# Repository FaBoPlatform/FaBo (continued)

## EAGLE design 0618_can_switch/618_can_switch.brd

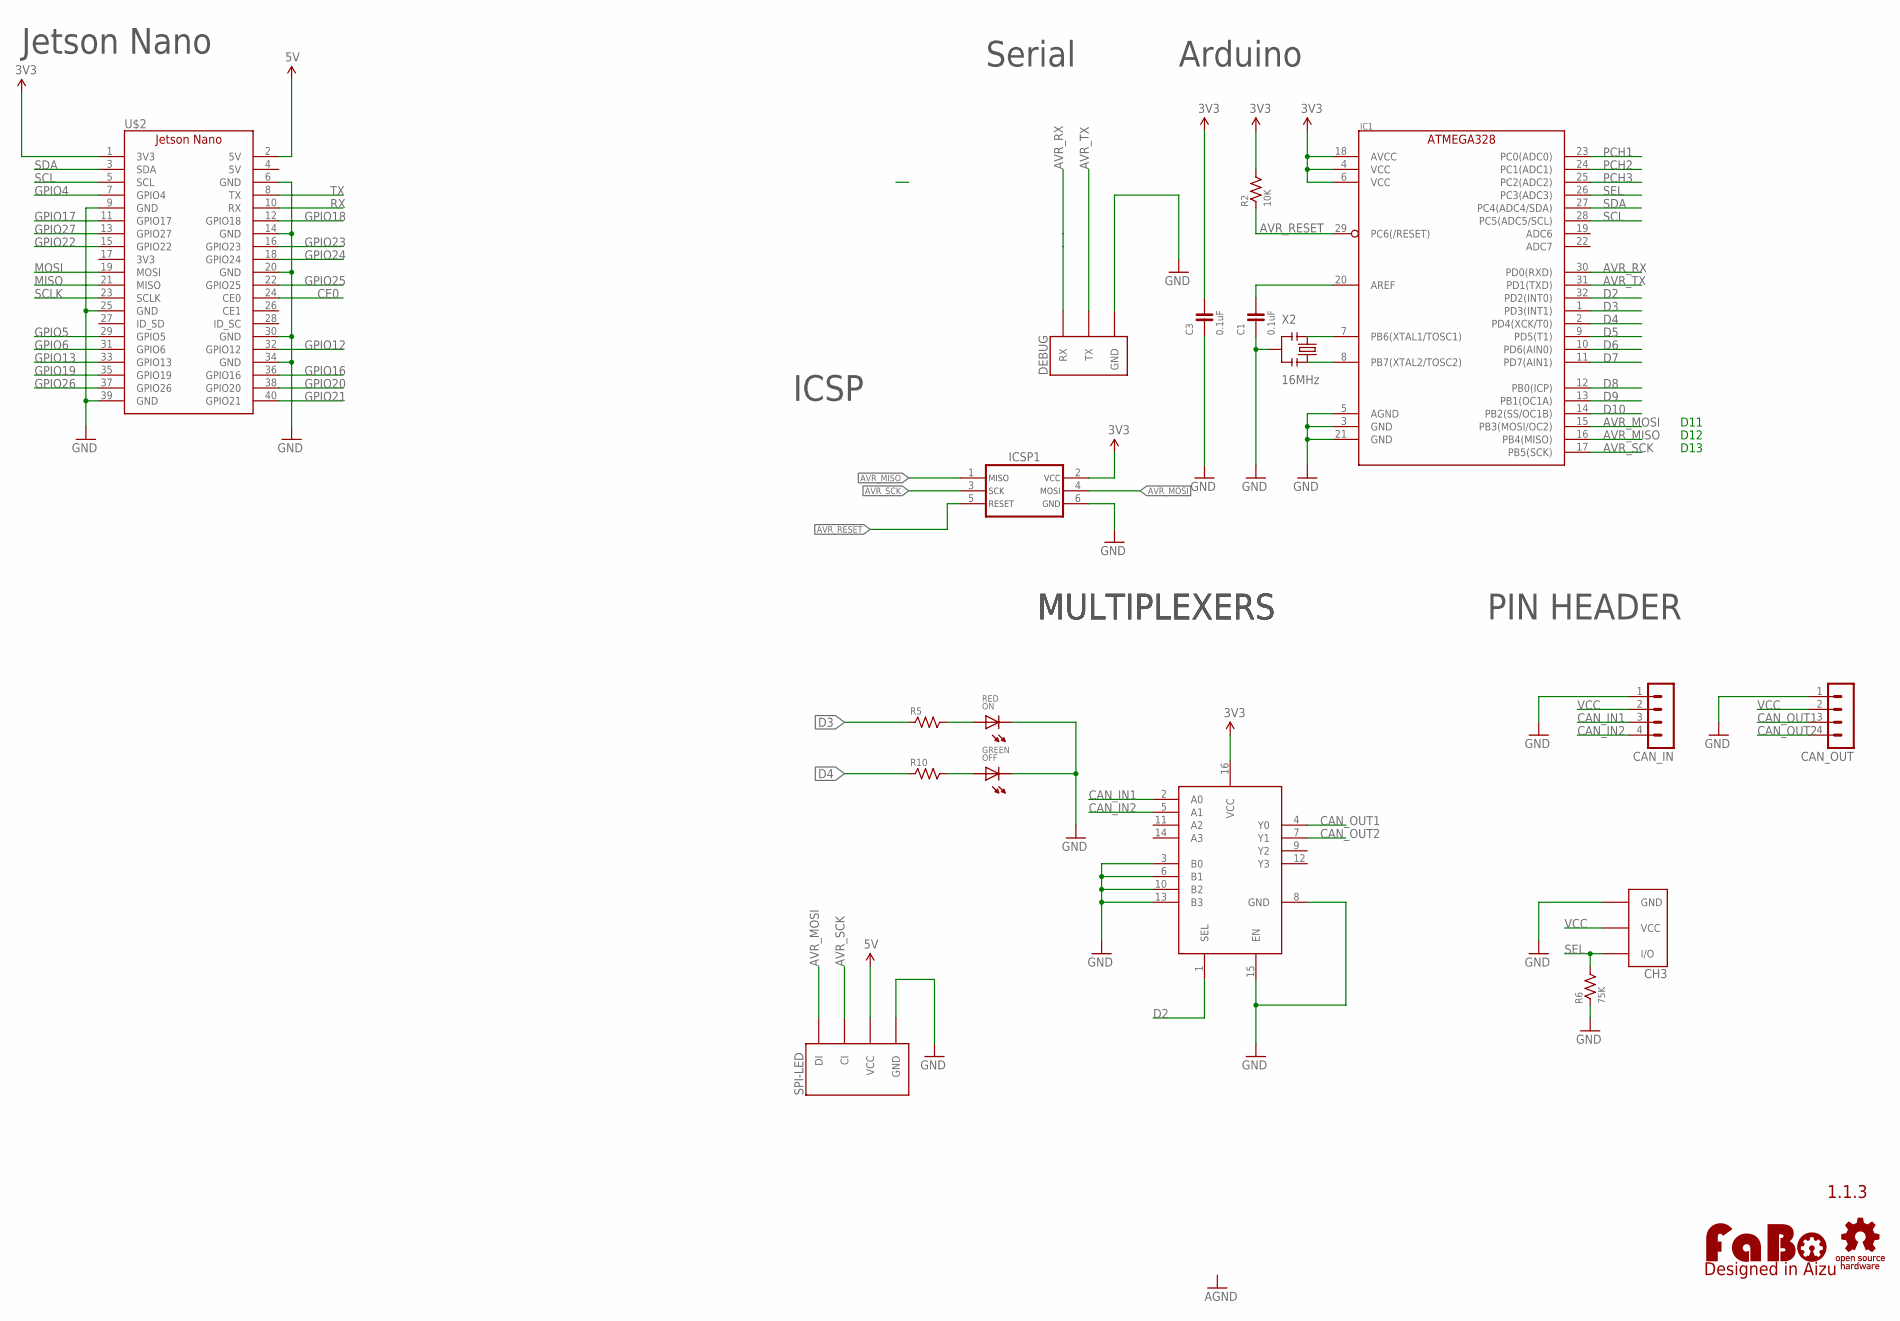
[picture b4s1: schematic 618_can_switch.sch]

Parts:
C1, C3: 0.1uF; 0603
CAN_IN: MA04-1
CAN_OUT: MA04-1
CH3: FABO_BRICK_3PIN-HEADER; FABO_BRICK_3PIN_HEADER
DEBUG: FABO_BRICK_3PIN_DEBUG
IC1: ATMEGA328P-AU; TQFP-32
IC3: MULTIPLEXERSMC74HC157A; TSSOP-16
ICSP1: ICSP_AVR-TC_NOHOLE; TC2030
LOGO1: LOGO_FABO-S; LOGO_FABO_S
OFF: GREEN; 0603
ON: RED; 0603
R2: 10K; 0603
R5, R10: 220; 0603
R6: 75K; 0603
SPI-LED: FABO-SPI-LED-B04B; SPI-B04B-PASK-1
U$2: JETSON_NANO_NOBORDER; JETSON_NANO_NOBOARDER
U$7: LOGO_OSHW-M_BOTTOM; LOGO_OSHW_M_BOTTOM
X2: 16MHz; CSTNE_V_C

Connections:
3V3: C3.2, IC1.4 (VCC), IC1.6 (VCC), IC1.18 (AVCC), IC3.16 (VCC), ICSP1.2, R2.2, U$2.1 (3V3)
5V: SPI-LED.VCC, U$2.2 (5V)
AVR_MISO: IC1.16 (PB4(MISO)), ICSP1.1
AVR_MOSI: IC1.15 (PB3(MOSI/OC2)), ICSP1.4, SPI-LED.DI
AVR_RESET: IC1.29 (PC6(/RESET)), ICSP1.5, R2.1
AVR_RX: DEBUG.RX, IC1.30 (PD0(RXD))
AVR_SCK: IC1.17 (PB5(SCK)), ICSP1.3, SPI-LED.CI
AVR_TX: DEBUG.TX, IC1.31 (PD1(TXD))
CAN_IN1: CAN_IN.3, IC3.2 (A0)
CAN_IN2: CAN_IN.4, IC3.5 (A1)
CAN_OUT1: CAN_OUT.3, IC3.4 (Y0)
CAN_OUT2: CAN_OUT.4, IC3.7 (Y1)
CE0: U$2.24 (CE0)
D2: IC1.32 (PD2(INT0)), IC3.1 (SEL)
D3: IC1.1 (PD3(INT1)), R5.1
D4: IC1.2 (PD4(XCK/T0)), R10.1
D5: IC1.9 (PD5(T1))
D6: IC1.10 (PD6(AIN0))
D7: IC1.11 (PD7(AIN1))
D8: IC1.12 (PB0(ICP))
D9: IC1.13 (PB1(OC1A))
D10: IC1.14 (PB2(SS/OC1B))
GND: C1.1, C3.1, CAN_IN.1, CAN_OUT.1, CH3.GND, DEBUG.GND, IC1.3 (GND), IC1.5 (AGND), IC1.21 (GND), IC3.3 (B0), IC3.6 (B1), IC3.8 (GND), IC3.10 (B2), IC3.13 (B3), IC3.15 (EN), ICSP1.6, OFF.CATHODE, ON.CATHODE, R6.1, SPI-LED.GND, U$2.6 (GND), U$2.9 (GND), U$2.14 (GND), U$2.20 (GND), U$2.25 (GND), U$2.30 (GND), U$2.34 (GND), U$2.39 (GND), X2.2
GPIO4: U$2.7 (GPIO4)
GPIO5: U$2.29 (GPIO5)
GPIO6: U$2.31 (GPIO6)
GPIO12: U$2.32 (GPIO12)
GPIO13: U$2.33 (GPIO13)
GPIO16: U$2.36 (GPIO16)
GPIO17: U$2.11 (GPIO17)
GPIO18: U$2.12 (GPIO18)
GPIO19: U$2.35 (GPIO19)
GPIO20: U$2.38 (GPIO20)
GPIO21: U$2.40 (GPIO21)
GPIO22: U$2.15 (GPIO22)
GPIO23: U$2.16 (GPIO23)
GPIO24: U$2.18 (GPIO24)
GPIO25: U$2.22 (GPIO25)
GPIO26: U$2.37 (GPIO26)
GPIO27: U$2.13 (GPIO27)
MISO: U$2.21 (MISO)
MOSI: U$2.19 (MOSI)
unnamed: C1.2, IC1.20 (AREF)
unnamed: IC1.8 (PB7(XTAL2/TOSC2)), X2.3
unnamed: IC1.7 (PB6(XTAL1/TOSC1)), X2.1
unnamed: ON.ANODE, R5.2
unnamed: OFF.ANODE, R10.2
PCH1: IC1.23 (PC0(ADC0))
PCH2: IC1.24 (PC1(ADC1))
PCH3: IC1.25 (PC2(ADC2))
RX: U$2.10 (RX)
SCL: IC1.28 (PC5(ADC5/SCL)), U$2.5 (SCL)
SCLK: U$2.23 (SCLK)
SDA: IC1.27 (PC4(ADC4/SDA)), U$2.3 (SDA)
SEL: CH3.I/O, IC1.26 (PC3(ADC3)), R6.2
TX: U$2.8 (TX)
VCC: CAN_IN.2, CAN_OUT.2, CH3.VCC

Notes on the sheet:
1.1.3
Jetson Nano
MULTIPLEXERS
PIN HEADER
D11
D12
D13
Arduino
Serial
ICSP

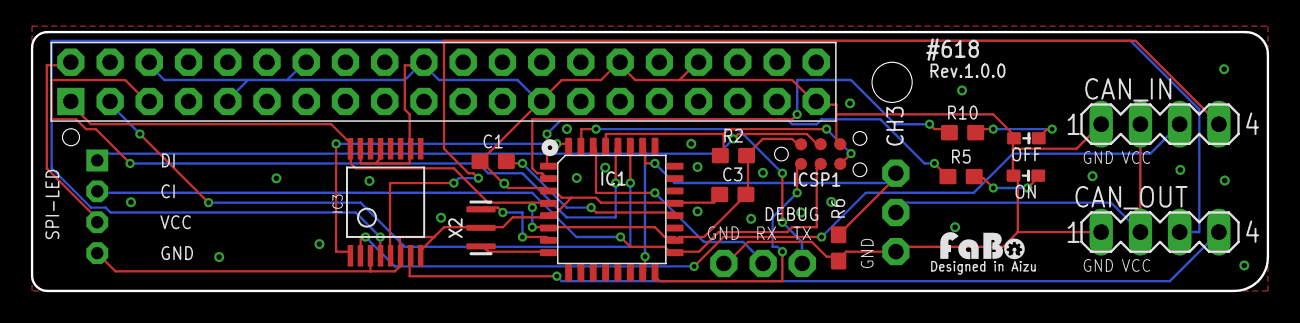
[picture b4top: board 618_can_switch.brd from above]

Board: 2 copper layers, 80.0 x 16.8 mm, 20 parts (0 on the bottom side), 25 nets.

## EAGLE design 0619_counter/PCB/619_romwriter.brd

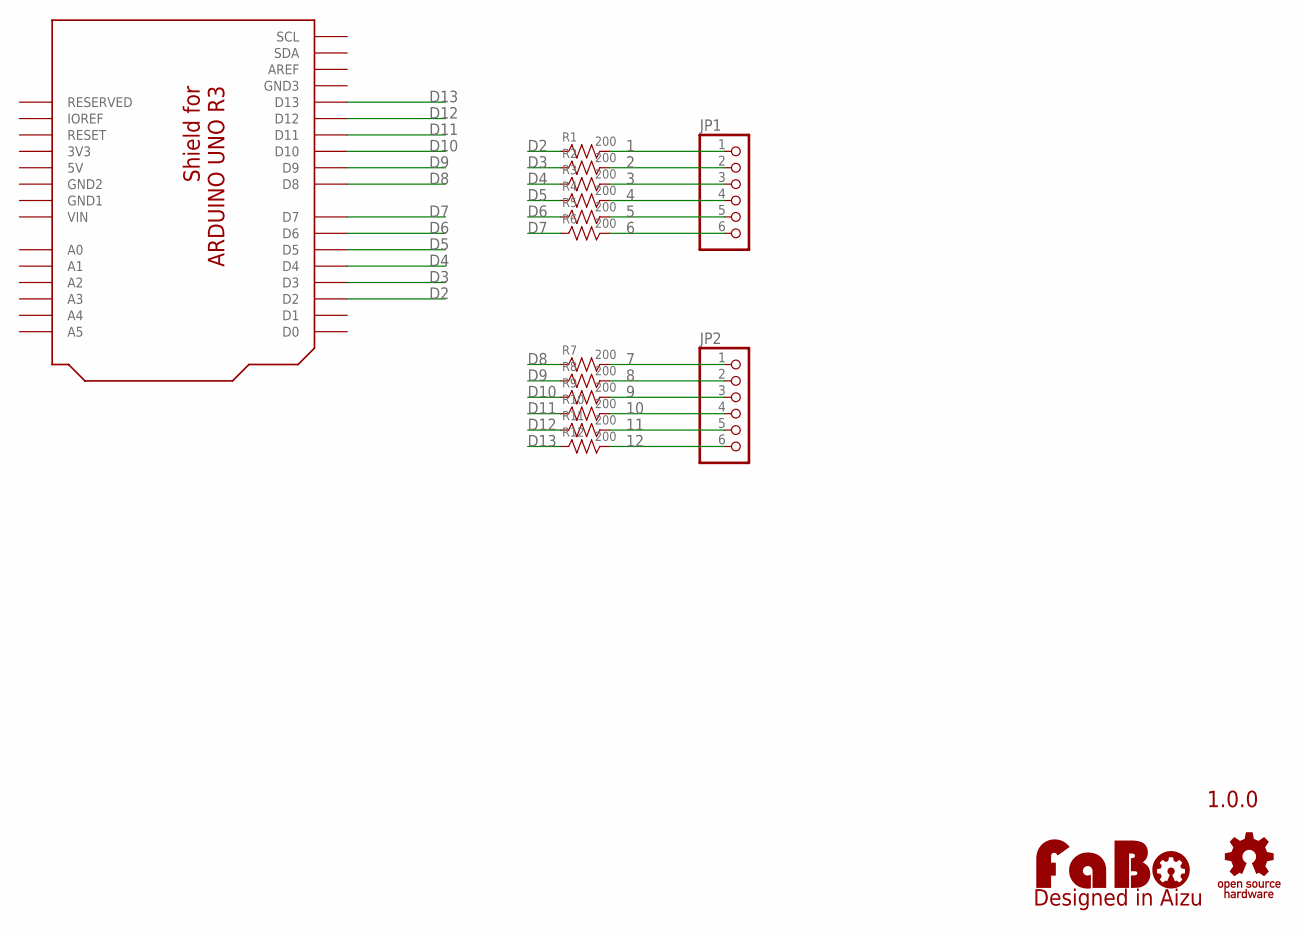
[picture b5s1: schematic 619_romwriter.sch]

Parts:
JP1, JP2: PINHD-1X6; 1X06
LOGO1: LOGO_FABO-M; LOGO_FABO_M
R1, R2, R3, R4, R5, R6, R7, R8, R9, R10, R11, R12: 200; 0603
U2: ARDUINO_UNO_R3_SHIELD-NOLABEL; ARDUINO_UNO_R3_NOLABEL
U$2: LOGO_OSHW-T_M; LOGO_OSHW_T_MS

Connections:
1: JP1.1, R1.2
2: JP1.2, R2.2
3: JP1.3, R3.2
3V3: U2.3V3
4: JP1.4, R4.2
5: JP1.5, R5.2
5V: U2.5V
6: JP1.6, R6.2
7: JP2.1, R7.2
8: JP2.2, R8.2
9: JP2.3, R9.2
10: JP2.4, R10.2
11: JP2.5, R11.2
12: JP2.6, R12.2
D2: R1.1, U2.D2
D3: R2.1, U2.D3
D4: R3.1, U2.D4
D5: R4.1, U2.D5
D6: R5.1, U2.D6
D7: R6.1, U2.D7
D8: R7.1, U2.D8
D9: R8.1, U2.D9
D10: R9.1, U2.D10
D11: R10.1, U2.D11
D12: R11.1, U2.D12
D13: R12.1, U2.D13
GND1: U2.GND1
GND2: U2.GND2
GND3: U2.GND3
VIN: U2.VIN

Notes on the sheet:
1.0.0

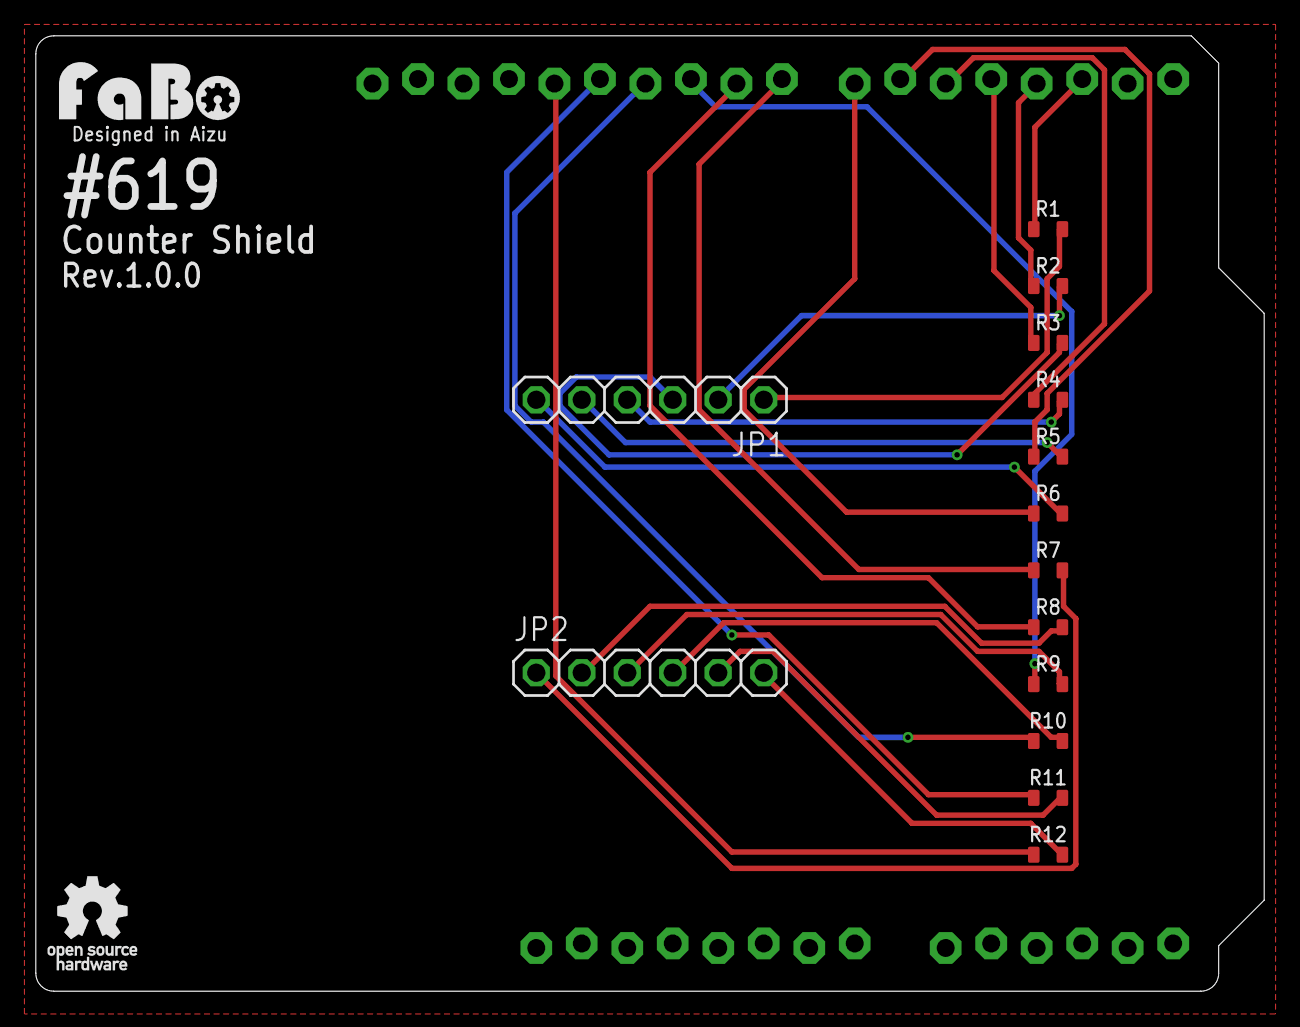
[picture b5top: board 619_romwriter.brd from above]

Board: 2 copper layers, 68.6 x 53.3 mm, 17 parts (0 on the bottom side), 24 nets.

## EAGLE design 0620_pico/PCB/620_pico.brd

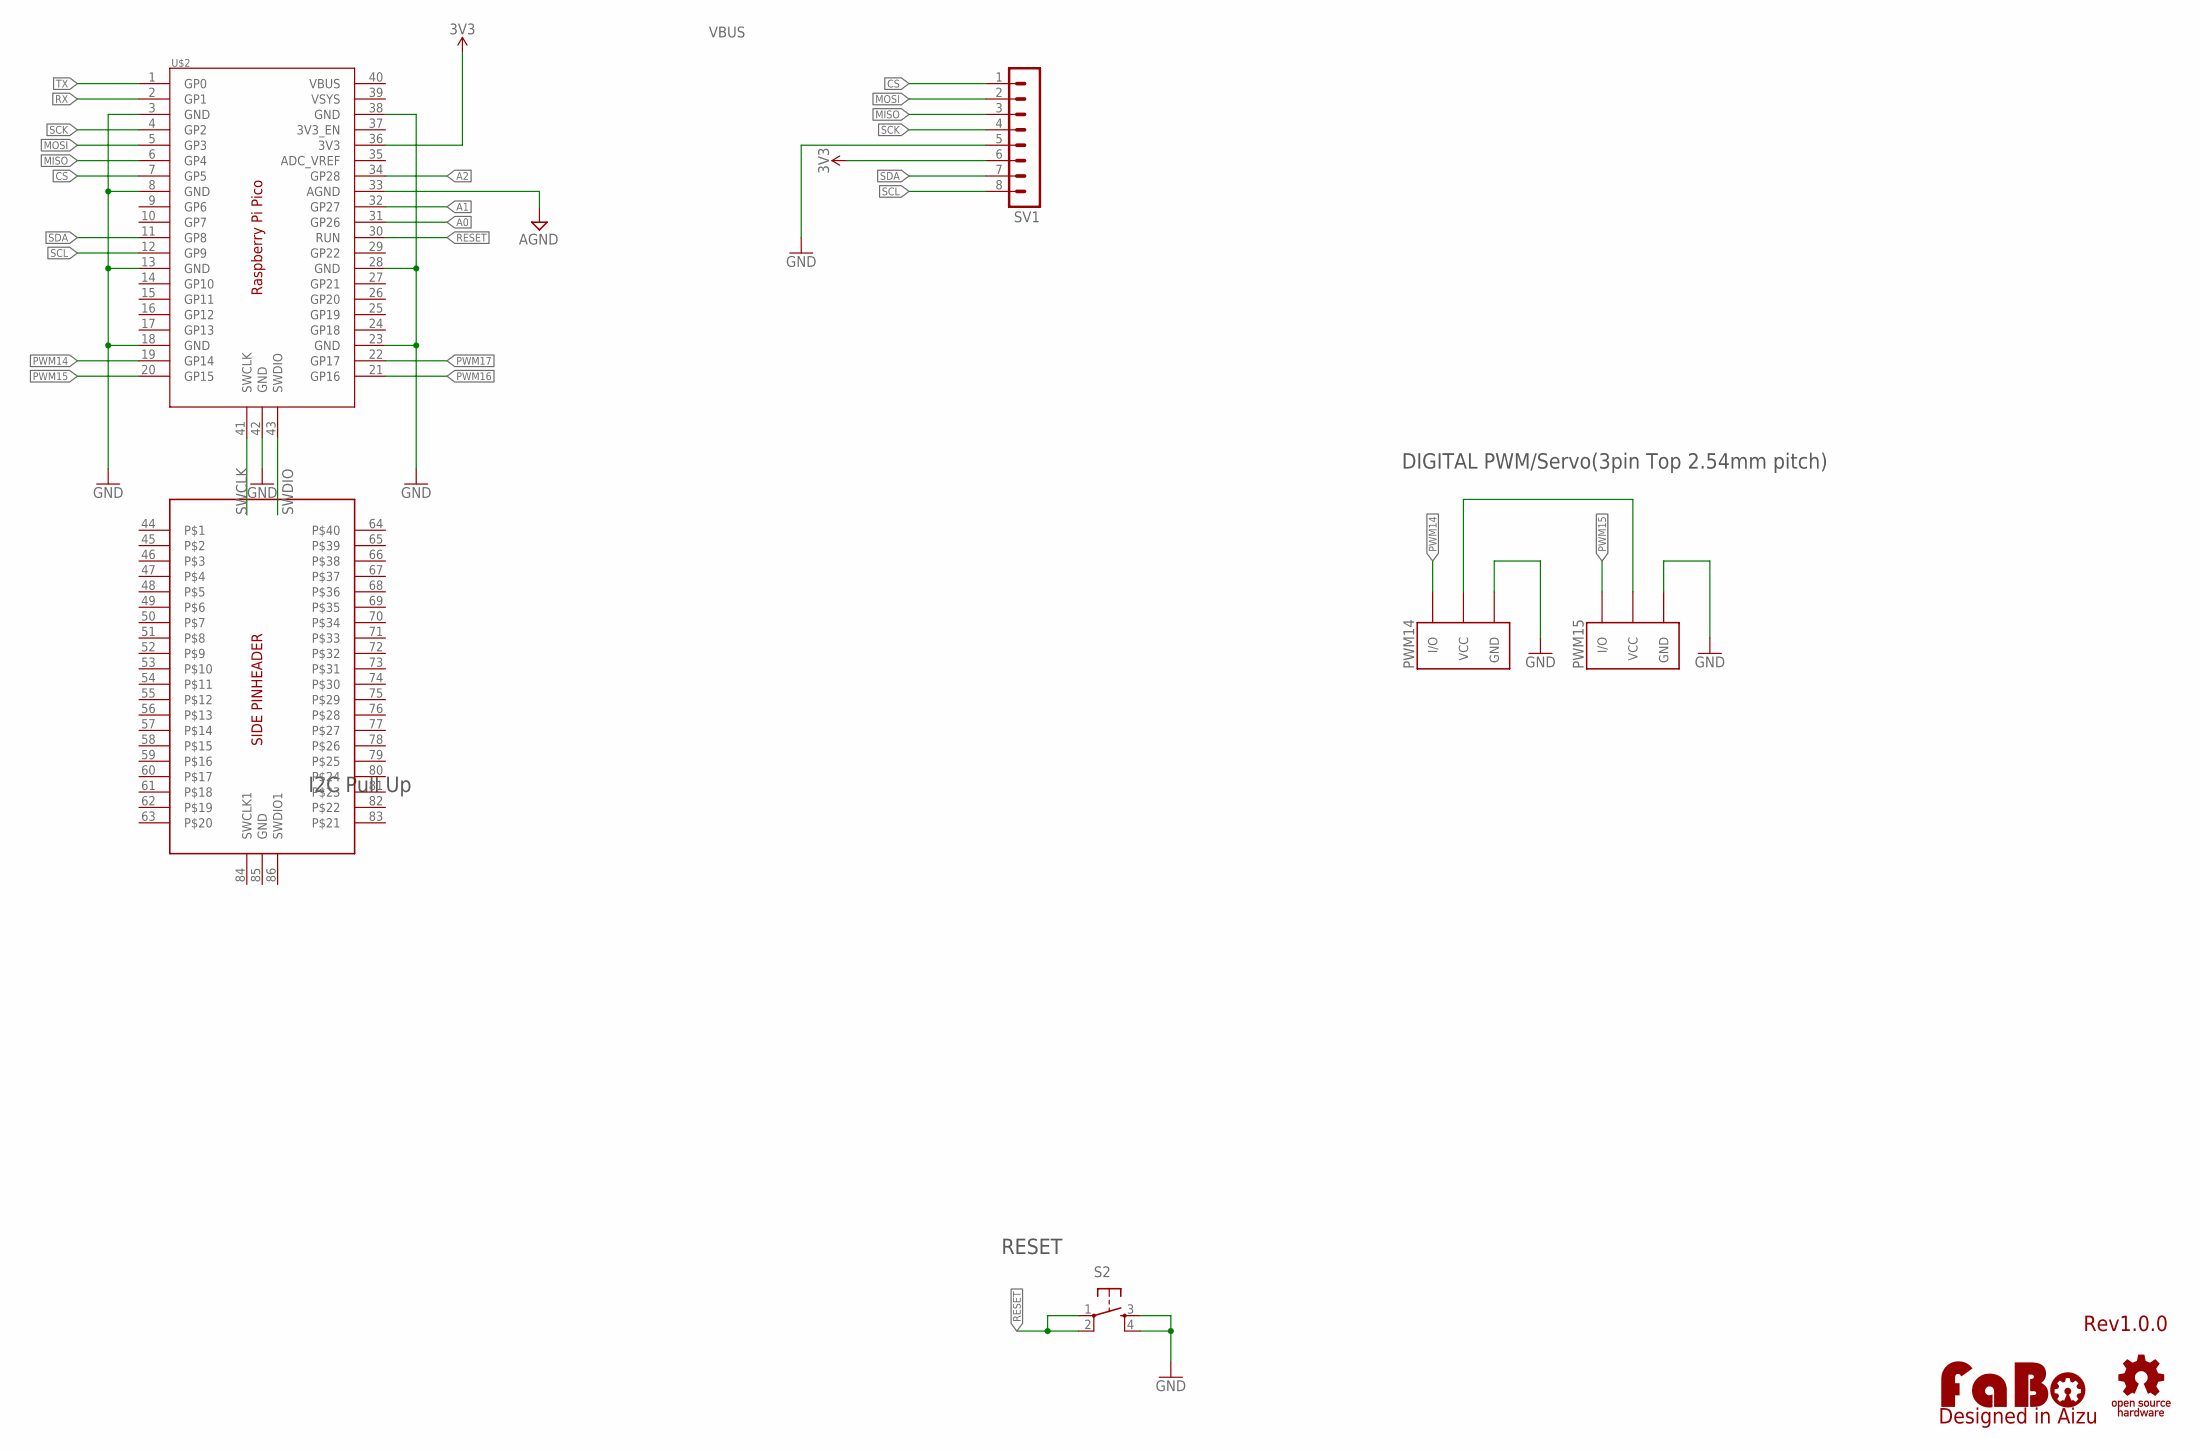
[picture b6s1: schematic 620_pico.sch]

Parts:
LOGO1: LOGO_OSHW-M_BOTTOM; LOGO_OSHW_M_BOTTOM
LOGO2: LOGO_FABO-M; LOGO_FABO_M
PWM14, PWM15: FABO_BRICK_3PIN-HEADER; FABO_BRICK_3PIN_HEADER
S2: TACT-SWITCH-SMD_KMR2; KMR2
SV1: MA08-1
U$2: RASPBERRY_PI_PICO_BOTH_TH_PINHEADER; RASPBERRY_PI_PICO_HEADER_BOTH

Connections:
3V3: SV1.6, U$2.36 (3V3)
A0: U$2.31 (GP26)
A1: U$2.32 (GP27)
A2: U$2.34 (GP28)
AGND: U$2.33 (AGND)
CS: SV1.1, U$2.7 (GP5)
GND: PWM14.GND, PWM15.GND, S2.3, S2.4, SV1.5, U$2.3 (GND), U$2.8 (GND), U$2.13 (GND), U$2.18 (GND), U$2.23 (GND), U$2.28 (GND), U$2.38 (GND), U$2.42 (GND)
MISO: SV1.3, U$2.6 (GP4)
MOSI: SV1.2, U$2.5 (GP3)
PWM14: PWM14.I/O, U$2.19 (GP14)
PWM15: PWM15.I/O, U$2.20 (GP15)
PWM16: U$2.21 (GP16)
PWM17: U$2.22 (GP17)
RESET: S2.1, S2.2, U$2.30 (RUN)
RX: U$2.2 (GP1)
SCK: SV1.4, U$2.4 (GP2)
SCL: SV1.8, U$2.12 (GP9)
SDA: SV1.7, U$2.11 (GP8)
SWCLK: U$2.41 (SWCLK)
SWDIO: U$2.43 (SWDIO)
TX: U$2.1 (GP0)
VBUS: PWM14.VCC, PWM15.VCC

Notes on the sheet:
Rev1.0.0
DIGITAL PWM/Servo(3pin Top 2.54mm pitch)
RESET
I2C Pull Up

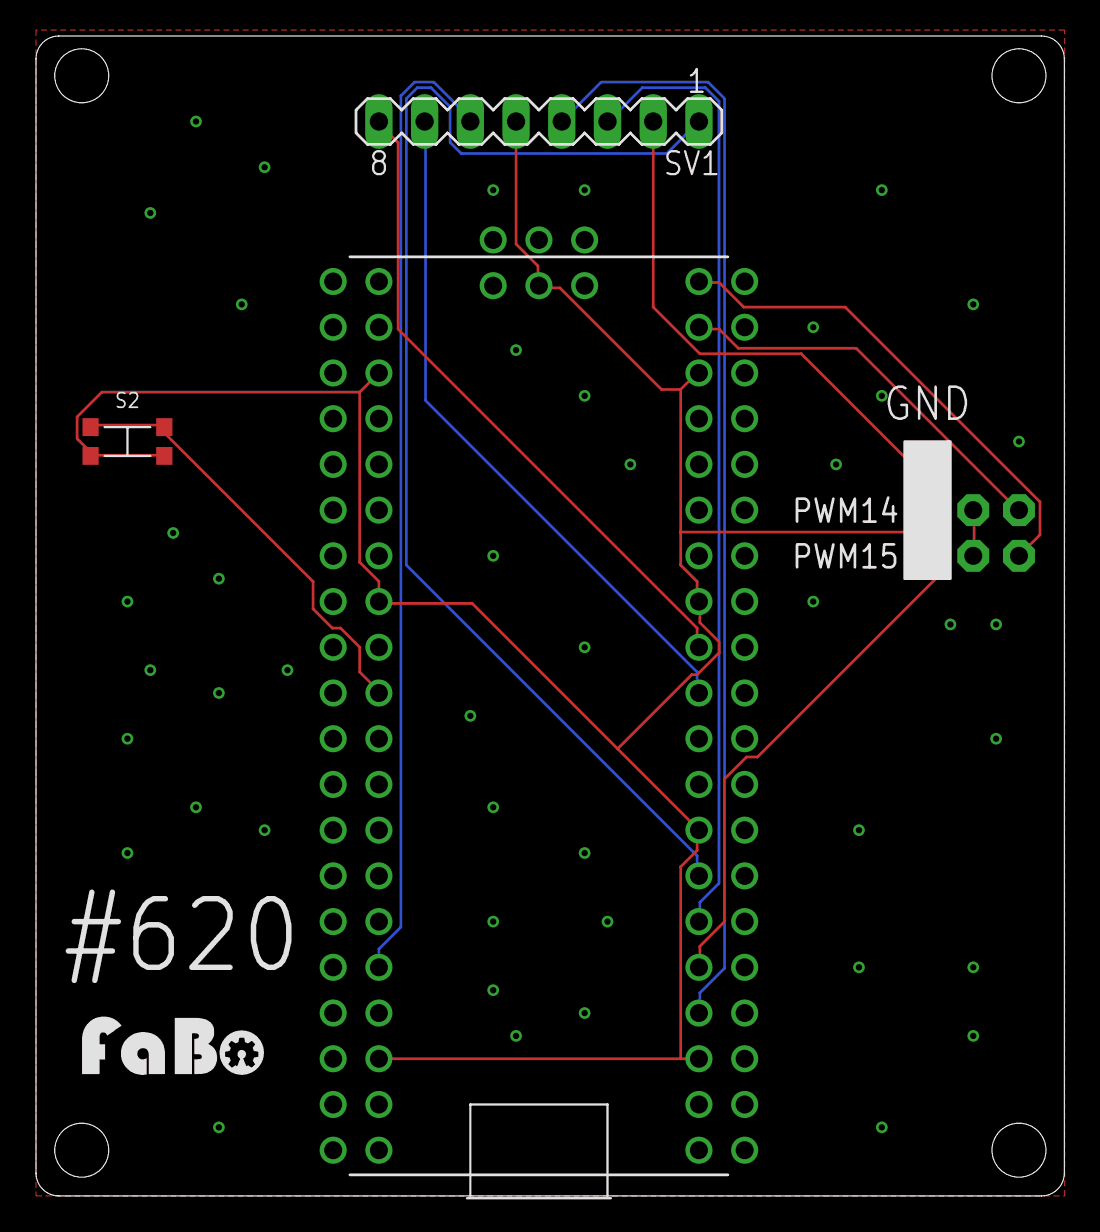
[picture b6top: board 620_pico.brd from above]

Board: 2 copper layers, 57.1 x 64.4 mm, 7 parts (0 on the bottom side), 12 nets.

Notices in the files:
parts and their libraries:
FaBo-Resistors: Released under the Creative Commons Attribution-ShareAlike 4.0 License
https://creativecommons.org/licenses/by-sa/4.0
FaBo-etc: Released under the Creative Commons
